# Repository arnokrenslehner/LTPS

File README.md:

# LTPS
LTPS (**L**ow **T**emperature **P**ower **S**ystem) is a power supply board designed for high-altitude balloon applications.
It provides three step-up converters and load switches as well as an ADC which can be read via I2C. <br>
The smb connector on the upper left side is part of the "remove before flight" circuitry, you can use a shorted out smb plug to disable the whole
LTPS system.

The board measures 120*100mm, its 4 layers.

## PCB Production and part procurement  
The design is optimized to the standard JLC-PCB 4-layer process.
I bought the parts from Mouser, all automotive types. Because it's just a private project 
I can't provide you with a "clean" BOM.

This version here incorporates all bugfixes from the first one I built:

One can see the bodge on the upper left of the PCB, I also fixed up some spacing, etc.

The board is designed to hold three "SAFT M52 LiMnO2" cells which are ideal for high-altitude ballooning, but expensive, one can 
use some other (lithium cells) in "C" size.

Please consult the schematic and the according datasheets for modifications etc.

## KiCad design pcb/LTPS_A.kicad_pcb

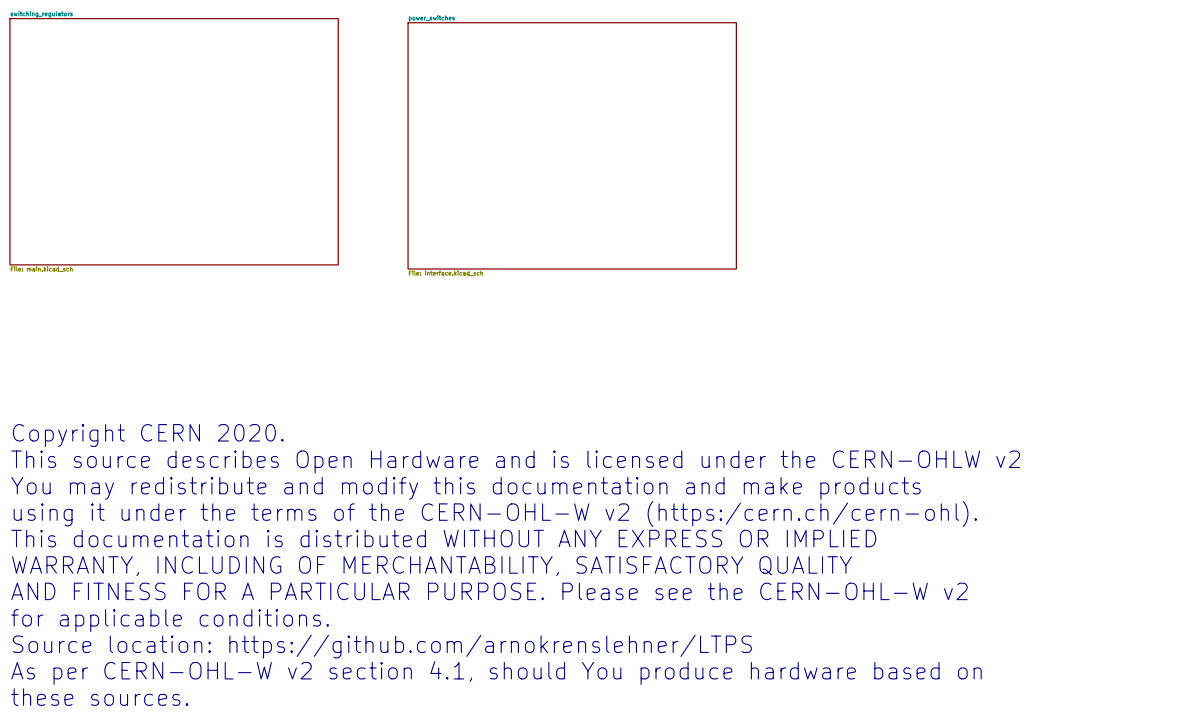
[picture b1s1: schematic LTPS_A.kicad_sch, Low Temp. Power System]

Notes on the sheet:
Copyright CERN 2020. This source describes Open Hardware and is licensed under the CERN-OHLW v2 You may redistribute and modify this documentation and make products using it under the terms of the CERN-OHL-W v2 (https:/cern.ch/cern-ohl). This documentation is distributed WITHOUT ANY EXPRESS OR IMPL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

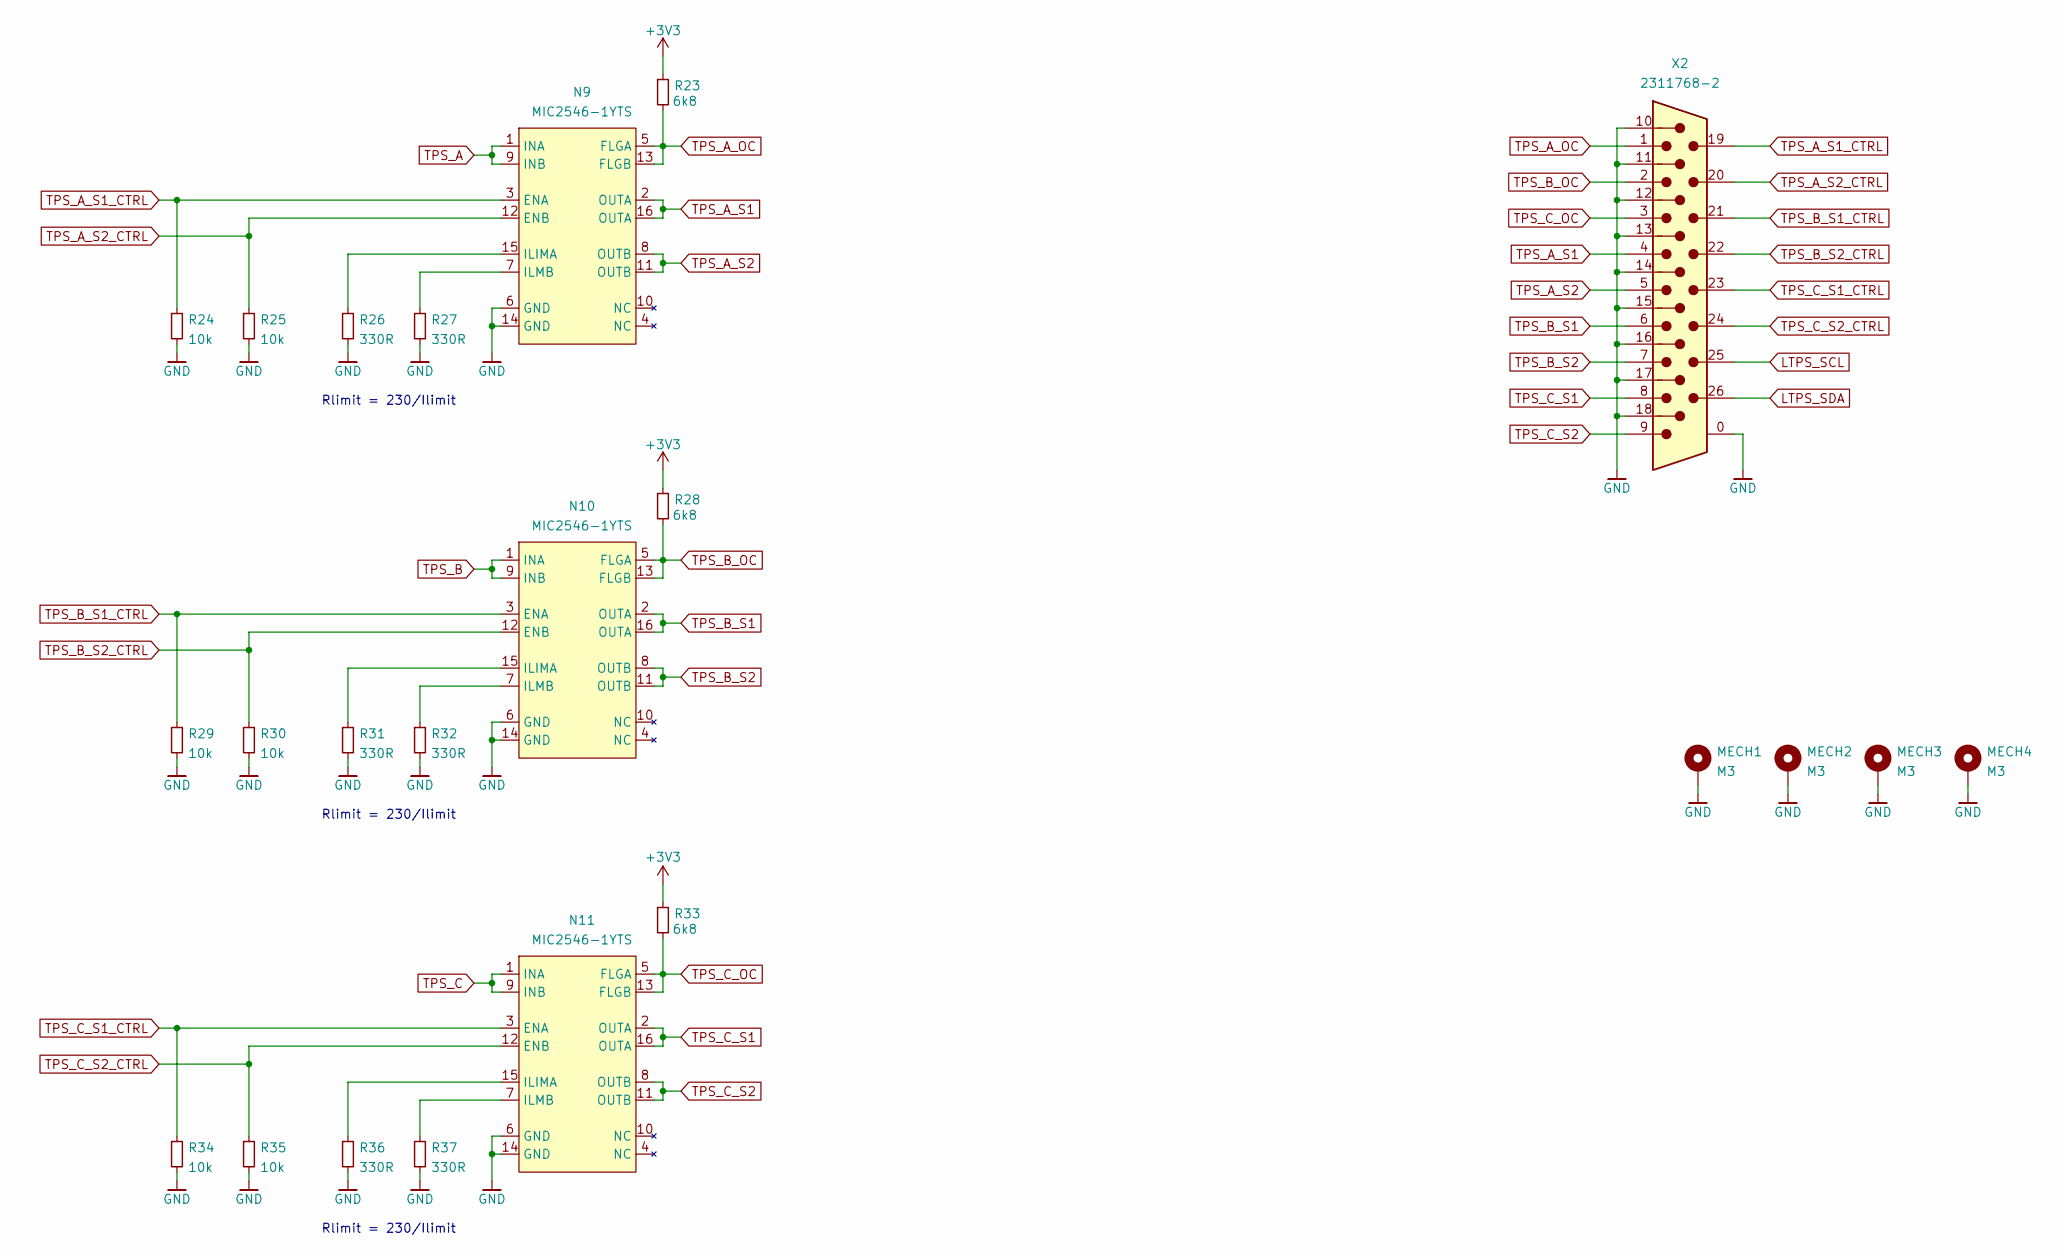
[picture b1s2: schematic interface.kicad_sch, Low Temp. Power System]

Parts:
MECH1, MECH2, MECH3, MECH4: M3; MountingHole_3.2mm_M3_ISO7380_Pad_TopBottom
N9, N10, N11: MIC2546-1YTS; TSSOP-16_4.4x5mm_P0.65mm
R23, R28, R33: 6k8; R_0603_1608Metric
R24, R25, R29, R30, R34, R35: 10k; R_0603_1608Metric
R26, R27, R31, R32, R36, R37: 330R; R_0603_1608Metric
X2: 2311768-2; 23117682

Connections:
+3V3: R23.1, R28.1, R33.1; also elsewhere on the board
GND: MECH1.1, MECH2.1, MECH3.1, MECH4.1, N9.6 (GND), N9.14 (GND), N10.6 (GND), N10.14 (GND), N11.6 (GND), N11.14 (GND), R24.2, R25.2, R26.2, R27.2, R29.2, R30.2, R31.2, R32.2, R34.2, R35.2, R36.2, R37.2, X2.0, X2.10, X2.11, X2.12, X2.13, X2.14, X2.15, X2.16, X2.17, X2.18; also elsewhere on the board
LTPS_SCL: X2.25; also elsewhere on the board
LTPS_SDA: X2.26; also elsewhere on the board
unnamed: N9.7 (ILMB), R27.1
unnamed: N9.15 (ILIMA), R26.1
unnamed: N10.7 (ILMB), R32.1
unnamed: N10.15 (ILIMA), R31.1
unnamed: N11.7 (ILMB), R37.1
unnamed: N11.15 (ILIMA), R36.1
TPS_A: N9.1 (INA), N9.9 (INB); also elsewhere on the board
TPS_A_OC: N9.5 (FLGA), N9.13 (FLGB), R23.2, X2.1
TPS_A_S1: N9.2 (OUTA), N9.16 (OUTA), X2.4
TPS_A_S1_CTRL: N9.3 (ENA), R24.1, X2.19
TPS_A_S2: N9.8 (OUTB), N9.11 (OUTB), X2.5
TPS_A_S2_CTRL: N9.12 (ENB), R25.1, X2.20
TPS_B: N10.1 (INA), N10.9 (INB); also elsewhere on the board
TPS_B_OC: N10.5 (FLGA), N10.13 (FLGB), R28.2, X2.2
TPS_B_S1: N10.2 (OUTA), N10.16 (OUTA), X2.6
TPS_B_S1_CTRL: N10.3 (ENA), R29.1, X2.21
TPS_B_S2: N10.8 (OUTB), N10.11 (OUTB), X2.7
TPS_B_S2_CTRL: N10.12 (ENB), R30.1, X2.22
TPS_C: N11.1 (INA), N11.9 (INB); also elsewhere on the board
TPS_C_OC: N11.5 (FLGA), N11.13 (FLGB), R33.2, X2.3
TPS_C_S1: N11.2 (OUTA), N11.16 (OUTA), X2.8
TPS_C_S1_CTRL: N11.3 (ENA), R34.1, X2.23
TPS_C_S2: N11.8 (OUTB), N11.11 (OUTB), X2.9
TPS_C_S2_CTRL: N11.12 (ENB), R35.1, X2.24

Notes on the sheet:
Rlimit = 230/Ilimit

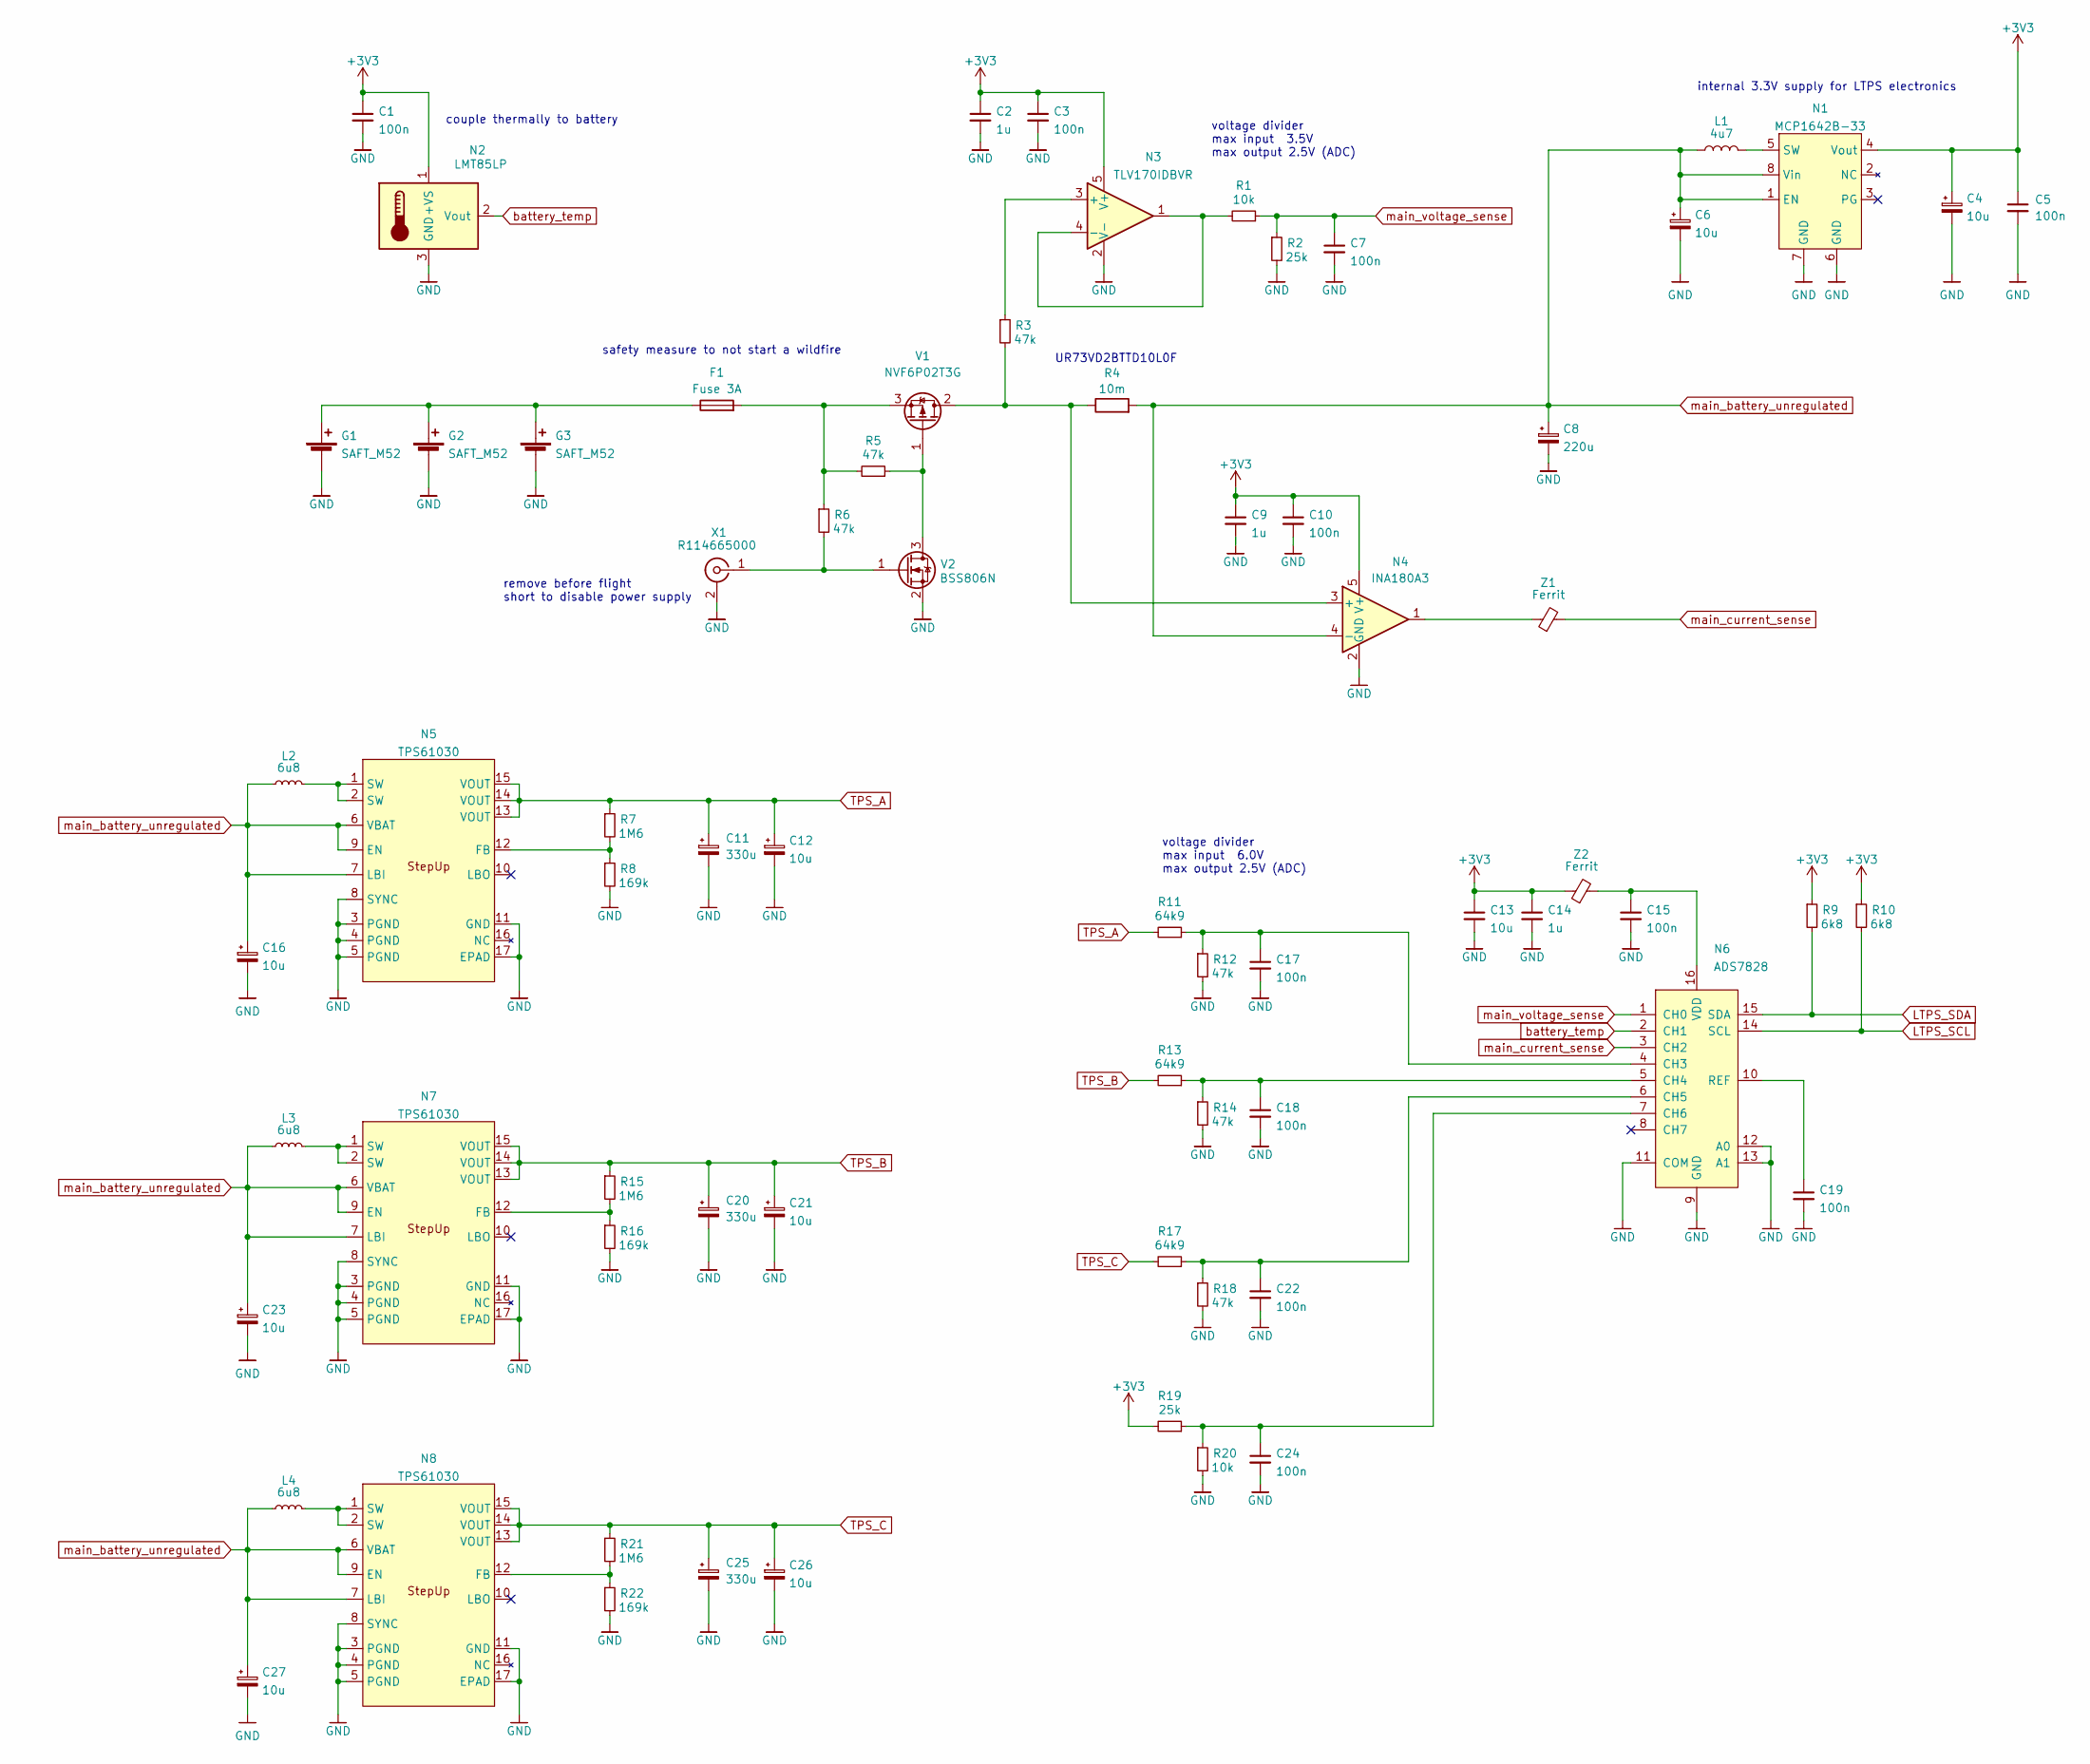
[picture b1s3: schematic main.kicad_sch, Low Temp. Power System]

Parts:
C1, C3, C5, C7, C10, C15, C17, C18, C19, C22, C24: 100n; C_0805_2012Metric
C2, C9, C14: 1u; C_0805_2012Metric
C4, C6, C12, C13, C16, C21, C23, C26, C27: 10u; C_1206_3216Metric
C8: 220u; CP_EIA-7343-30_AVX-N
C11, C20, C25: 330u; CP_EIA-7343-30_AVX-N
F1: Fuse 3A; Fuse_1206_3216Metric
G1, G2, G3: SAFT_M52
L1: 4u7; WE-TPC_5818_582892
L2, L3, L4: 6u8; L_Bourns_SRP7028A_7.3x6.6mm
N1: MCP1642B-33; MSOP-8_3x3mm_P0.65mm
N2: LMT85LP; TO-92_HandSolder
N3: TLV170IDBVR; TSOT-23-5
N4: INA180A3; SOT-23-5
N5, N7, N8: TPS61030; TSSOP-16-1EP_4.4x5mm_P0.65mm_EP3x3mm_ThermalVias
N6: ADS7828; TSSOP-16_4.4x5mm_P0.65mm
R1, R20: 10k; R_0603_1608Metric
R2, R19: 25k; R_0603_1608Metric
R3, R5, R6, R12, R14, R18: 47k; R_0603_1608Metric
R4: 10m; R_1206_3216Metric
R7, R15, R21: 1M6; R_0603_1608Metric
R8, R16, R22: 169k; R_0603_1608Metric
R9, R10: 6k8; R_0603_1608Metric
R11, R13, R17: 64k9; R_0603_1608Metric
V1: NVF6P02T3G; SOT-223-3_TabPin2
V2: BSS806N; SOT-23
X1: R114665000; SMB_Jack_Vertical
Z1, Z2: Ferrit; L_0603_1608Metric

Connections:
+3V3: C1.1, C2.1, C3.1, C4.1, C5.1, C9.1, C10.1, C13.1, C14.1, N1.4 (Vout), N2.1 (+VS), N3.5 (V+), N4.5 (V+), R9.1, R10.1, R19.2, Z2.1; also elsewhere on the board
GND: C1.2, C2.2, C3.2, C4.2, C5.2, C6.2, C7.2, C8.2, C9.2, C10.2, C11.2, C12.2, C13.2, C14.2, C15.2, C16.2, C17.2, C18.2, C19.2, C20.2, C21.2, C22.2, C23.2, C24.2, C25.2, C26.2, C27.2, G1.2 (-), G2.2 (-), G3.2 (-), N1.6 (GND), N1.7 (GND), N2.3 (GND), N3.2 (V-), N4.2 (GND), N5.3 (PGND), N5.4 (PGND), N5.5 (PGND), N5.8 (SYNC), N5.11 (GND), N5.17 (EPAD), N6.9 (GND), N6.11 (COM), N6.12 (A0), N6.13 (A1), N7.3 (PGND), N7.4 (PGND), N7.5 (PGND), N7.8 (SYNC), N7.11 (GND), N7.17 (EPAD), N8.3 (PGND), N8.4 (PGND), N8.5 (PGND), N8.8 (SYNC), N8.11 (GND), N8.17 (EPAD), R2.2, R8.2, R12.2, R14.2, R16.2, R18.2, R20.2, R22.2, V2.2 (S), X1.2 (Ext); also elsewhere on the board
LTPS_SCL: N6.14 (SCL), R10.2; also elsewhere on the board
LTPS_SDA: N6.15 (SDA), R9.2; also elsewhere on the board
unnamed: C15.1, N6.16 (VDD), Z2.2
unnamed: C17.1, N6.4 (CH3), R11.1, R12.1
unnamed: C18.1, N6.5 (CH4), R13.1, R14.1
unnamed: C19.1, N6.10 (REF)
unnamed: C22.1, N6.6 (CH5), R17.1, R18.1
unnamed: C24.1, N6.7 (CH6), R19.1, R20.1
unnamed: F1.1, G1.1 (+), G2.1 (+), G3.1 (+)
unnamed: F1.2, R5.2, R6.1, V1.3 (S)
unnamed: L1.2, N1.5 (SW)
unnamed: L2.2, N5.1 (SW), N5.2 (SW)
unnamed: L3.2, N7.1 (SW), N7.2 (SW)
unnamed: L4.2, N8.1 (SW), N8.2 (SW)
unnamed: N3.1, N3.4 (-), R1.2
unnamed: N3.3 (+), R3.1
unnamed: N4.1, Z1.1
unnamed: N4.3 (+), R3.2, R4.1, V1.2 (D)
unnamed: N5.12 (FB), R7.2, R8.1
unnamed: N7.12 (FB), R15.2, R16.1
unnamed: N8.12 (FB), R21.2, R22.1
unnamed: R5.1, V1.1 (G), V2.3 (D)
unnamed: R6.2, V2.1 (G), X1.1 (In)
TPS_A: C11.1, C12.1, N5.13 (VOUT), N5.14 (VOUT), N5.15 (VOUT), R7.1, R11.2; also elsewhere on the board
TPS_B: C20.1, C21.1, N7.13 (VOUT), N7.14 (VOUT), N7.15 (VOUT), R13.2, R15.1; also elsewhere on the board
TPS_C: C25.1, C26.1, N8.13 (VOUT), N8.14 (VOUT), N8.15 (VOUT), R17.2, R21.1; also elsewhere on the board
battery_temp: N2.2 (Vout), N6.2 (CH1)
main_battery_unregulated: C6.1, C8.1, C16.1, C23.1, C27.1, L1.1, L2.1, L3.1, L4.1, N1.1 (EN), N1.8 (Vin), N4.4 (-), N5.6 (VBAT), N5.7 (LBI), N5.9 (EN), N7.6 (VBAT), N7.7 (LBI), N7.9 (EN), N8.6 (VBAT), N8.7 (LBI), N8.9 (EN), R4.2
main_current_sense: N6.3 (CH2), Z1.2
main_voltage_sense: C7.1, N6.1 (CH0), R1.1, R2.1

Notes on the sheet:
couple thermally to battery
internal 3.3V supply for LTPS electronics
UR73VD2BTTD10L0F
safety measure to not start a wildfire
voltage divider max input 3.5V max output 2.5V (ADC)
remove before flight short to disable power supply
voltage divider max input 6.0V max output 2.5V (ADC)

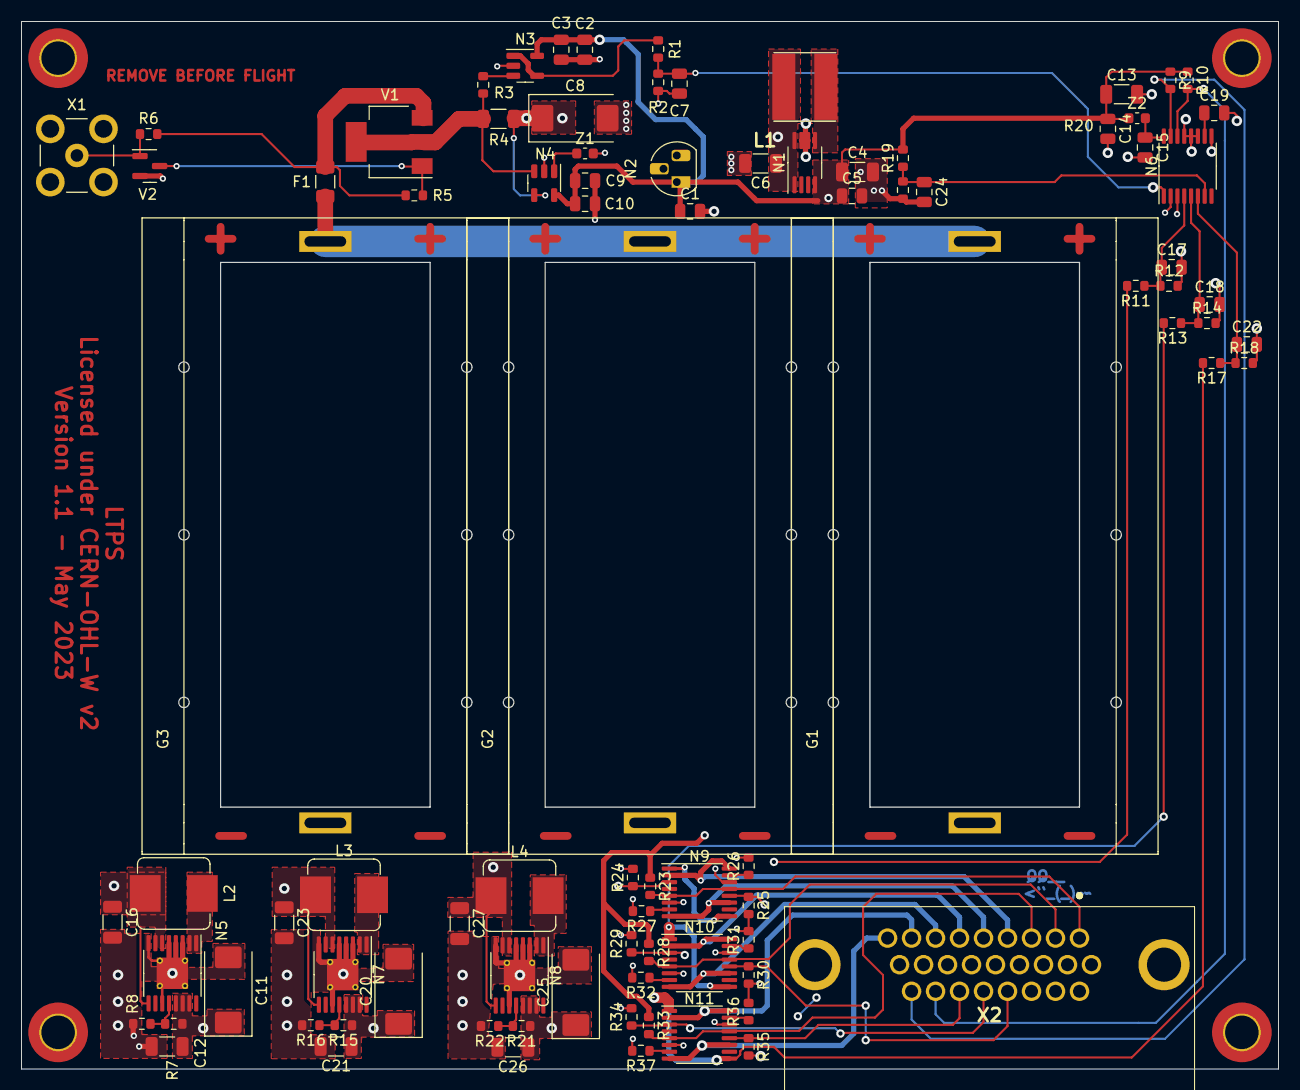
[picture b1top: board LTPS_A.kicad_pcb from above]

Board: 4 copper layers, 120.0 x 100.0 mm, 93 parts (0 on the bottom side), 53 nets.

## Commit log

2023-06-26 added pictures
2023-06-26 exif
2023-06-26 fixed license

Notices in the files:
pcb/LTPS_A.kicad_pcb:
Licensed under CERN-OHL-W v2
pcb/LTPS_A.kicad_sch:
As per CERN-OHL-W v2 section 4.1, should You produce hardware based on
